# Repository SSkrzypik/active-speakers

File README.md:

The project involves active speakers inspired by the Tonsil Maestro S. The power amplifier driving the speakers consists of four TDA7294 chips. For the crossover network and sound tone adjustments, a DSP Adau1701 is used. The power supply is sourced from a toroidal transformer, and the section is enhanced with an EMI filter and a soft-start circuit. Additionally, the master speaker features an extra board that controls an OLED display and serves as a Bluetooth audio source.

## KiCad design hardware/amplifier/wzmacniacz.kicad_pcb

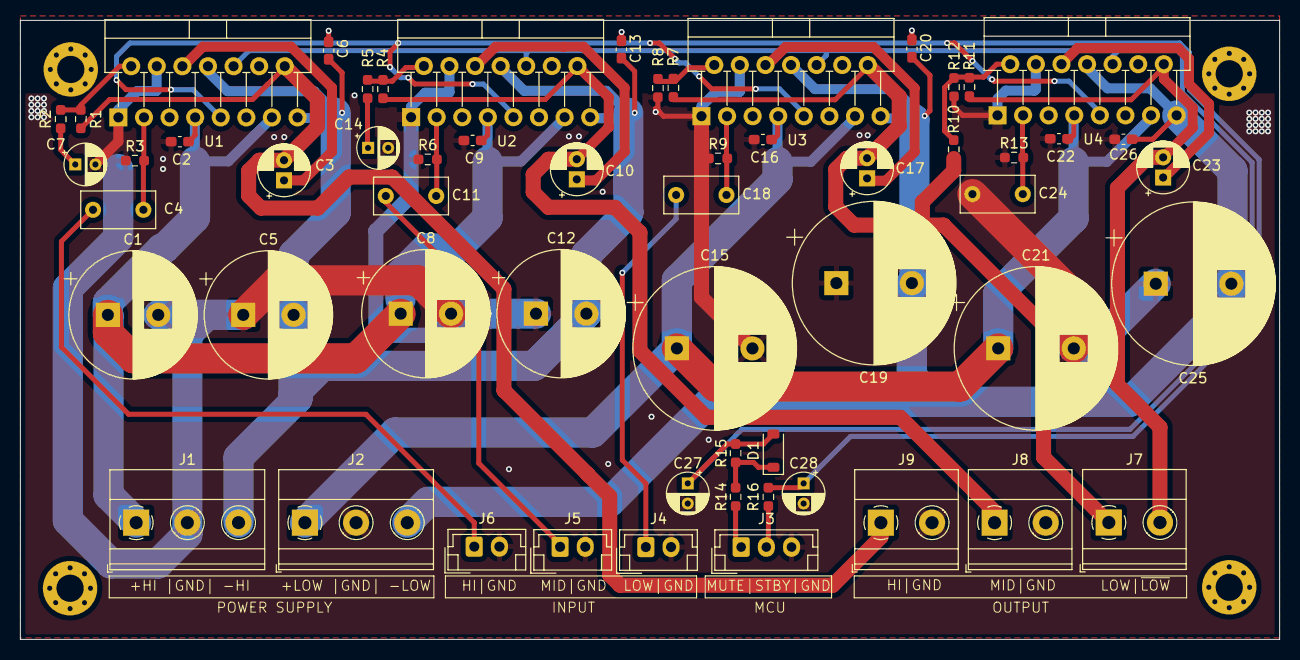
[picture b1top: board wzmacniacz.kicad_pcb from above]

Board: 2 copper layers, 125.0 x 61.4 mm, 62 parts (0 on the bottom side), 31 nets.

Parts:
C1, C5, C8, C12: 1000uF; CP_Radial_D12.5mm_P5.00mm
C2, C6, C9, C13, C16, C20, C22, C26: 100nF; C_0603_1608Metric_Pad1.08x0.95mm_HandSolder
C3, C10, C17, C23: 22uF; CP_Radial_D5.0mm_P2.00mm
C4, C11: 470nF; C_Rect_L7.2mm_W3.5mm_P5.00mm_FKS2_FKP2_MKS2_MKP2
C7, C14, C27, C28: 22uF; CP_Radial_D4.0mm_P2.00mm
C15, C19, C21, C25: 2200uF; CP_Radial_D16.0mm_P7.50mm
C18, C24: 560nF; C_Rect_L7.2mm_W3.5mm_P5.00mm_FKS2_FKP2_MKS2_MKP2
D1: 1N4148WT; D_SOD-123
H1, H2, H3, H4: MountingHole; MountingHole_2.7mm_Pad_Via
J1, J2: Conn_01x03; TerminalBlock_Phoenix_MKDS-1,5-3-5.08_1x03_P5.08mm_Horizont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
J3: Conn_01x03; JST_EH_B3B-EH-A_1x03_P2.50mm_Vertical
J4, J5, J6: Conn_01x02; JST_EH_B2B-EH-A_1x02_P2.50mm_Vertical
J7, J8, J9: Conn_01x02; TerminalBlock_Phoenix_MKDS-1,5-2-5.08_1x02_P5.08mm_Horizont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
R1, R3, R4, R6, R7, R9, R10, R11, R13, R16: 22K; R_0603_1608Metric_Pad0.98x0.95mm_HandSolder
R2, R5, R8, R12: 680; R_0603_1608Metric_Pad0.98x0.95mm_HandSolder
R14: 10K; R_0603_1608Metric_Pad0.98x0.95mm_HandSolder
R15: 30K; R_0603_1608Metric_Pad0.98x0.95mm_HandSolder
U1, U2, U3, U4: TDA7294; TO-220-15_P2.54x2.54mm_StaggerOdd_Lead4.58mm_Vertical

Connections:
+VS_HI/MID: C1.1, C2.2, C8.1, C9.2, J1.1, U1.7 (+Vs), U1.13 (+Vs), U2.7 (+Vs), U2.13 (+Vs)
+VS_LOW: C15.1, C16.2, C21.1, C22.2, J2.1, U3.7 (+Vs), U3.13 (+Vs), U4.7 (+Vs), U4.13 (+Vs)
-VS_HI/MID: C5.2, C6.2, C12.2, C13.2, J1.3, U1.8 (-Vs), U1.15 (-Vs), U2.8 (-Vs), U2.15 (-Vs)
-VS_LOW: C19.2, C20.2, C25.2, C26.2, J2.3, U3.8 (-Vs), U3.15 (-Vs), U4.8 (-Vs), U4.15 (-Vs)
/CTRL_MUTE: J3.1, R14.1
/CTRL_STBY: J3.2, R16.2
/IN_HIGH: C4.1, J6.1
/IN_LOW: C18.1, J4.1
/IN_MID: C11.1, J5.1
/MUTE: C27.1, D1.2 (A), R15.2, U1.10 (MUTE), U2.10 (MUTE), U3.10 (MUTE), U4.10 (MUTE)
/OUT_HIGH: C3.2, J9.1, R1.1, U1.14
/OUT_LOW+: C17.2, J7.1, R7.1, R10.1, U3.14
/OUT_LOW-: C23.2, J7.2, R11.1, U4.14
/OUT_MID: C10.2, J8.1, R4.1, U2.14
/STBY: C28.1, R16.1, U1.9 (STBY), U2.9 (STBY), U3.9 (STBY), U4.9 (STBY)
GND: C1.2, C2.1, C5.1, C6.1, C7.2, C8.2, C9.1, C12.1, C13.1, C14.2, C15.2, C16.1, C19.1, C20.1, C21.2, C22.1, C24.1, C25.1, C26.1, C27.2, C28.2, J1.2, J2.2, J3.3, J4.2, J5.2, J6.2, J8.2, J9.2, R3.1, R6.1, R8.1, R9.1, R12.1, R13.1, U1.1 (SGND), U1.4 (SIG_GND), U2.1 (SGND), U2.4 (SIG_GND), U3.1 (SGND), U3.4 (SIG_GND), U4.1 (SGND), U4.4 (SIG_GND)
unnamed: C7.1, R2.1
unnamed: C14.1, R5.1
unnamed: D1.1 (K), R14.2, R15.1
unnamed: C4.2, R3.2, U1.3 (+)
unnamed: R1.2, R2.2, U1.2 (-)
unnamed: C3.1, U1.6 (BOOT)
unnamed: C11.2, R6.2, U2.3 (+)
unnamed: R4.2, R5.2, U2.2 (-)
unnamed: C10.1, U2.6 (BOOT)
unnamed: C18.2, R9.2, U3.3 (+)
unnamed: R7.2, R8.2, U3.2 (-)
unnamed: C17.1, U3.6 (BOOT)
unnamed: C24.2, R13.2, U4.3 (+)
unnamed: R10.2, R11.2, R12.2, U4.2 (-)
unnamed: C23.1, U4.6 (BOOT)

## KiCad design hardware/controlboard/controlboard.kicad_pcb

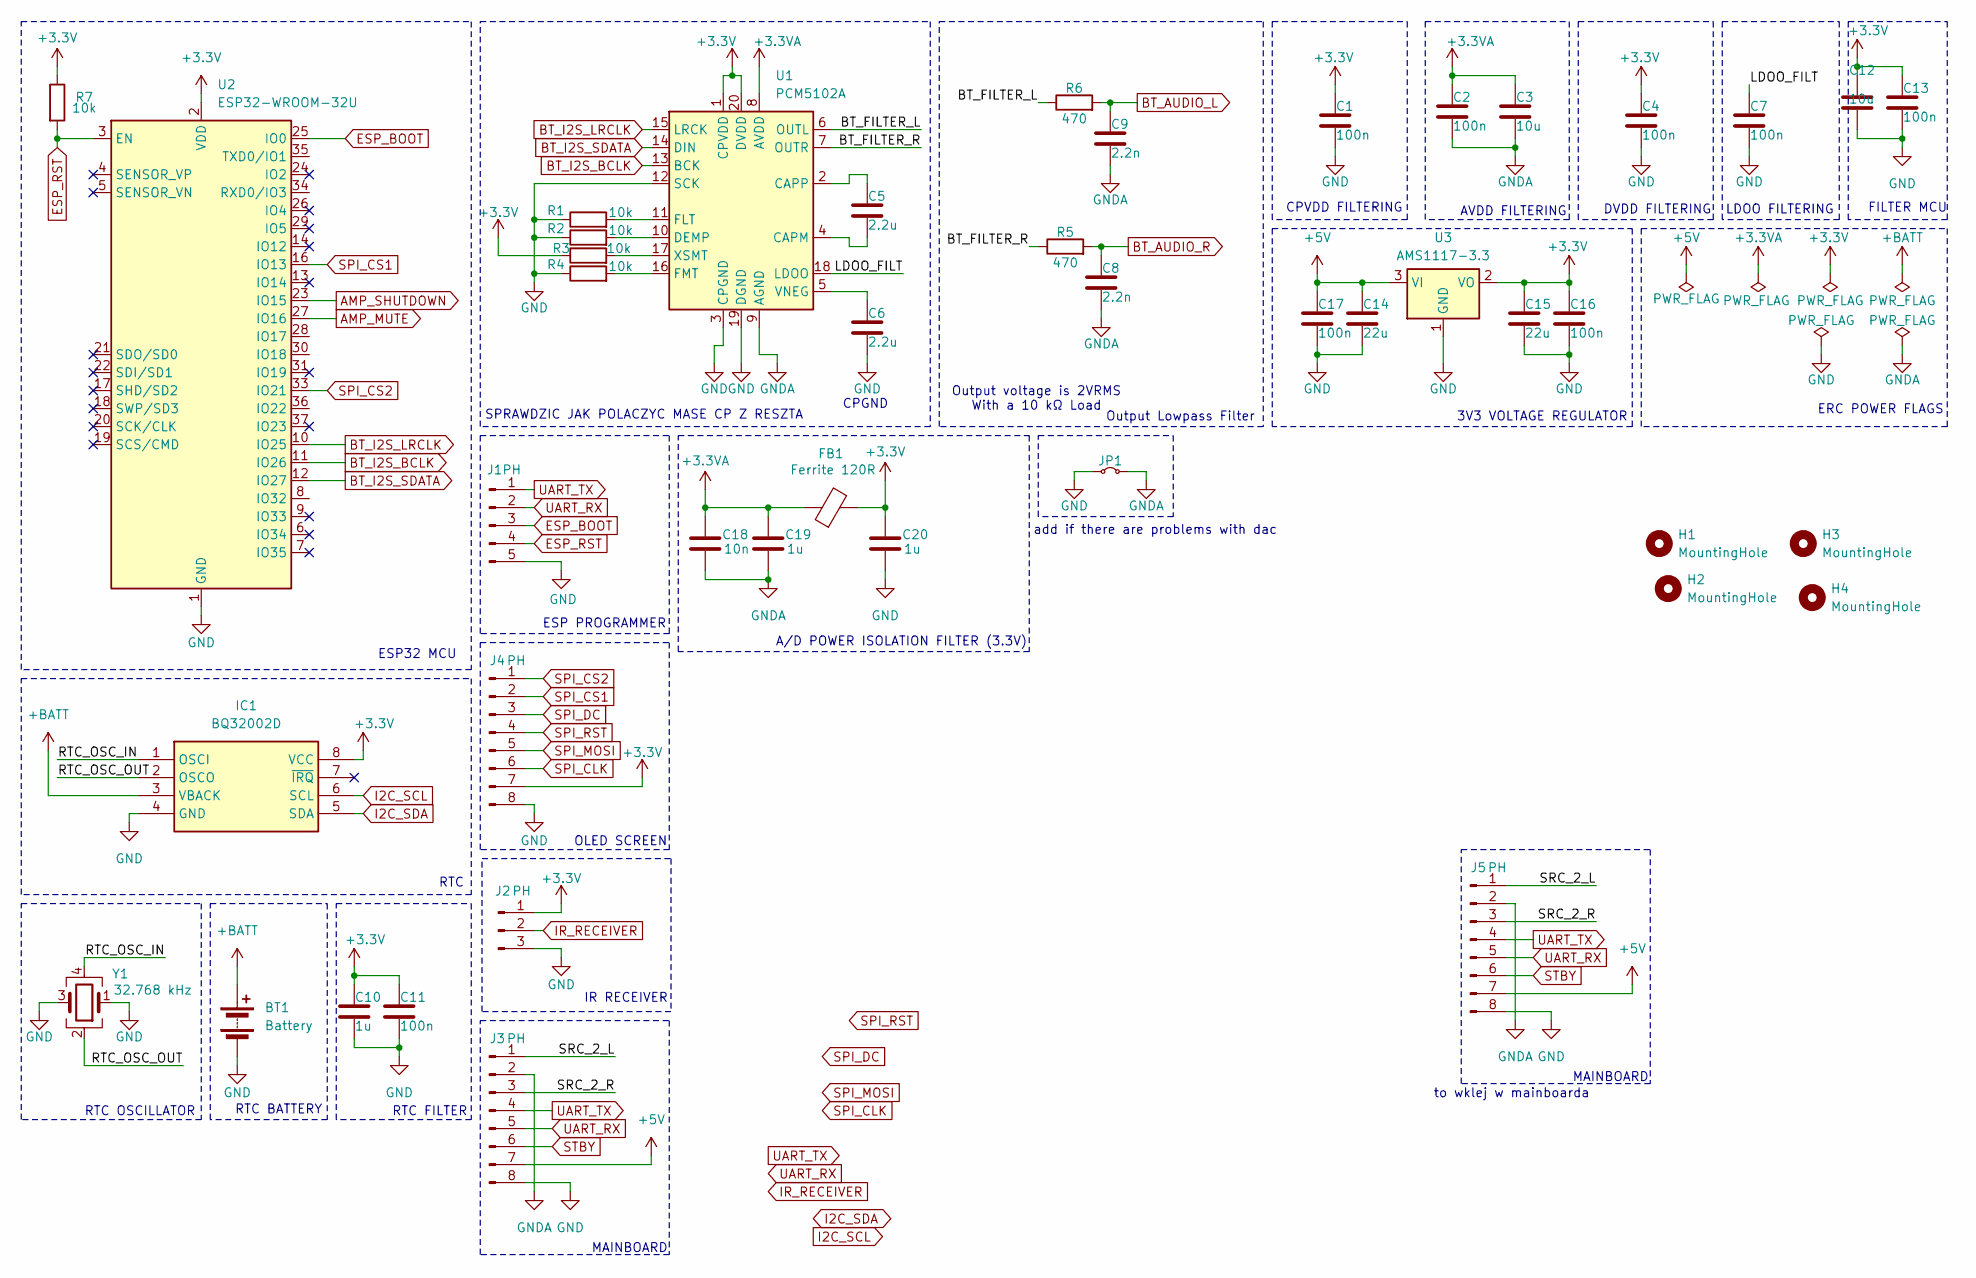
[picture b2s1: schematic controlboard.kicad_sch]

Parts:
BT1: Battery; BatteryHolder_LINX_BAT-HLD-012-SMT
C1, C2, C4, C7, C11, C13, C16, C17: 100n; C_0603_1608Metric_Pad1.08x0.95mm_HandSolder
C3, C12: 10u; C_0603_1608Metric_Pad1.08x0.95mm_HandSolder
C5, C6: 2.2u; C_0603_1608Metric_Pad1.08x0.95mm_HandSolder
C8, C9: 2.2n; C_0603_1608Metric_Pad1.08x0.95mm_HandSolder
C10, C19, C20: 1u; C_0603_1608Metric_Pad1.08x0.95mm_HandSolder
C14, C15: 22u; C_0603_1608Metric_Pad1.08x0.95mm_HandSolder
C18: 10n; C_0603_1608Metric_Pad1.08x0.95mm_HandSolder
FB1: Ferrite 120R; L_0805_2012Metric_Pad1.05x1.20mm_HandSolder
H1, H2, H3, H4: MountingHole; MountingHole_3.2mm_M3
IC1: BQ32002D; SOIC-8_3.9x4.9mm_P1.27mm; Mouser Part Number 595-BQ32002D
J1: PH; JST_PH_B5B-PH-K_1x05_P2.00mm_Vertical
J2: PH; JST_PH_B3B-PH-K_1x03_P2.00mm_Vertical
J3, J4: PH; JST_PH_B8B-PH-K_1x08_P2.00mm_Vertical
J5: PH
JP1: Jumper_2_Small_Bridged; R_1210_3225Metric_Pad1.30x2.65mm_HandSolder
R1, R2, R3, R4, R7: 10k; R_0603_1608Metric_Pad0.98x0.95mm_HandSolder
R5, R6: 470; R_0603_1608Metric_Pad0.98x0.95mm_HandSolder
U1: PCM5102A; TSSOP-20_4.4x6.5mm_P0.65mm
U2: ESP32-WROOM-32U
U3: AMS1117-3.3; SOT-223-3_TabPin2
Y1: 32.768 kHz; Crystal_SMD_7050-4Pin_7.0x5.0mm

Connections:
+3.3V: C1.1, C4.1, C10.1, C11.1, C12.1, C13.1, C15.1, C16.1, C20.1, FB1.2, IC1.8 (VCC), J2.1, J4.7, R3.1, R7.1, U1.1 (CPVDD), U1.20 (DVDD), U2.2 (VDD), U3.2 (VO)
+3.3VA: C2.1, C3.1, C18.1, C19.1, FB1.1, U1.8 (AVDD)
+5V: C14.1, C17.1, J3.7, J5.7, U3.3 (VI)
+BATT: BT1.1 (+), IC1.3 (VBACK)
/BT_FILTER_L: R6.1, U1.6 (OUTL)
/BT_FILTER_R: R5.1, U1.7 (OUTR)
/LDOO_FILT: C7.1, U1.18 (LDOO)
/RTC_OSC_IN: IC1.1 (OSCI), Y1.4
/RTC_OSC_OUT: IC1.2 (OSCO), Y1.2
/SRC_2_L: J3.1, J5.1
/SRC_2_R: J3.3, J5.3
AMP_MUTE: U2.27 (IO16)
AMP_SHUTDOWN: U2.23 (IO15)
BT_AUDIO_L: C9.1, R6.2
BT_AUDIO_R: C8.1, R5.2
BT_I2S_BCLK: U1.13 (BCK), U2.11 (IO26)
BT_I2S_LRCLK: U1.15 (LRCK), U2.10 (IO25)
BT_I2S_SDATA: U1.14 (DIN), U2.12 (IO27)
ESP_BOOT: J1.3, U2.25 (IO0)
ESP_RST: J1.4, R7.2, U2.3 (EN)
GND: BT1.2 (-), C1.2, C4.2, C6.2, C7.2, C10.2, C11.2, C12.2, C13.2, C14.2, C15.2, C16.2, C17.2, C20.2, IC1.4 (GND), J1.5, J2.3, J3.8, J4.8, J5.8, JP1.1 (A), R1.1, R2.1, R4.1, U1.3 (CPGND), U1.12 (SCK), U1.19 (DGND), U2.1 (GND), U2.15 (GND), U2.38 (GND), U2.39 (GND), U3.1 (GND), Y1.1, Y1.3
GNDA: C2.2, C3.2, C8.2, C9.2, C18.2, C19.2, J3.2, J5.2, JP1.2 (B), U1.9 (AGND)
I2C_SCL: IC1.6 (SCL)
I2C_SDA: IC1.5 (SDA)
IR_RECEIVER: J2.2
unnamed: C5.2, U1.4 (CAPM)
unnamed: C5.1, U1.2 (CAPP)
unnamed: R2.2, U1.10 (DEMP)
unnamed: R1.2, U1.11 (FLT)
unnamed: R4.2, U1.16 (FMT)
unnamed: C6.1, U1.5 (VNEG)
unnamed: R3.2, U1.17 (XSMT)
SPI_CLK: J4.6
SPI_CS1: J4.2, U2.16 (IO13)
SPI_CS2: J4.1, U2.33 (IO21)
SPI_DC: J4.3
SPI_MOSI: J4.5
SPI_RST: J4.4
STBY: J3.6, J5.6
UART_RX: J1.2, J3.5, J5.5
UART_TX: J1.1, J3.4, J5.4

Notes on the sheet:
ESP32 MCU
ERC POWER FLAGS
RTC FILTER
AVDD FILTERING
ESP PROGRAMMER
MAINBOARD
FILTER MCU
Output voltage is 2VRMS With a 10 kΩ Load
to wklej w mainboarda
RTC OSCILLATOR
3V3 VOLTAGE REGULATOR
RTC BATTERY
RTC
CPGND
add if there are problems with dac
OLED SCREEN
IR RECEIVER
Output Lowpass Filter
CPVDD FILTERING
LDOO FILTERING
SPRAWDZIC JAK POLACZYC MASE CP Z RESZTA
DVDD FILTERING
A/D POWER ISOLATION FILTER (3.3V)

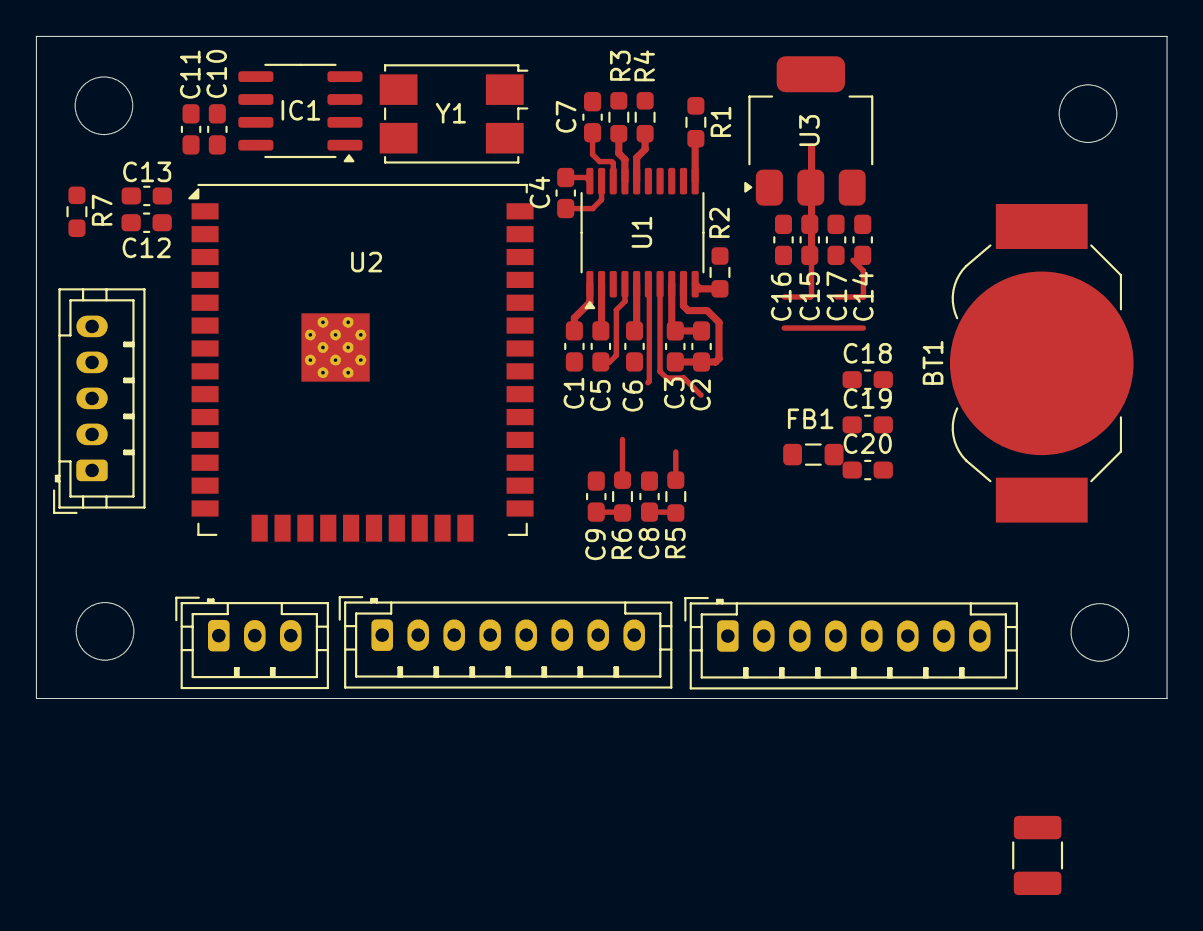
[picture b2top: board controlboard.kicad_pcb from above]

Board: 2 copper layers, 62.8 x 36.8 mm, 43 parts (0 on the bottom side), 29 nets.

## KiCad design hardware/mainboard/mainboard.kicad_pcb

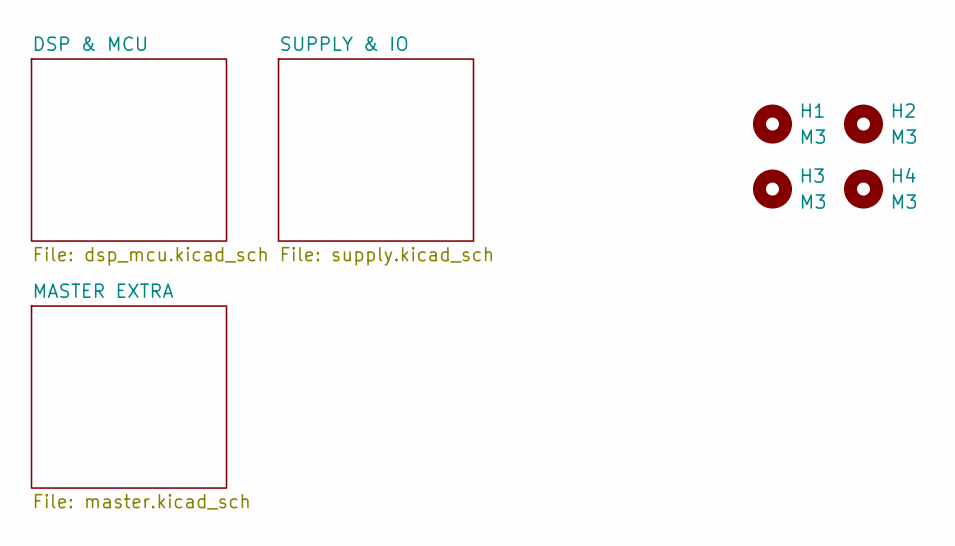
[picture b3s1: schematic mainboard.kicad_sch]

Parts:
H1, H2, H3, H4: M3; MountingHole_2.7mm_M2.5

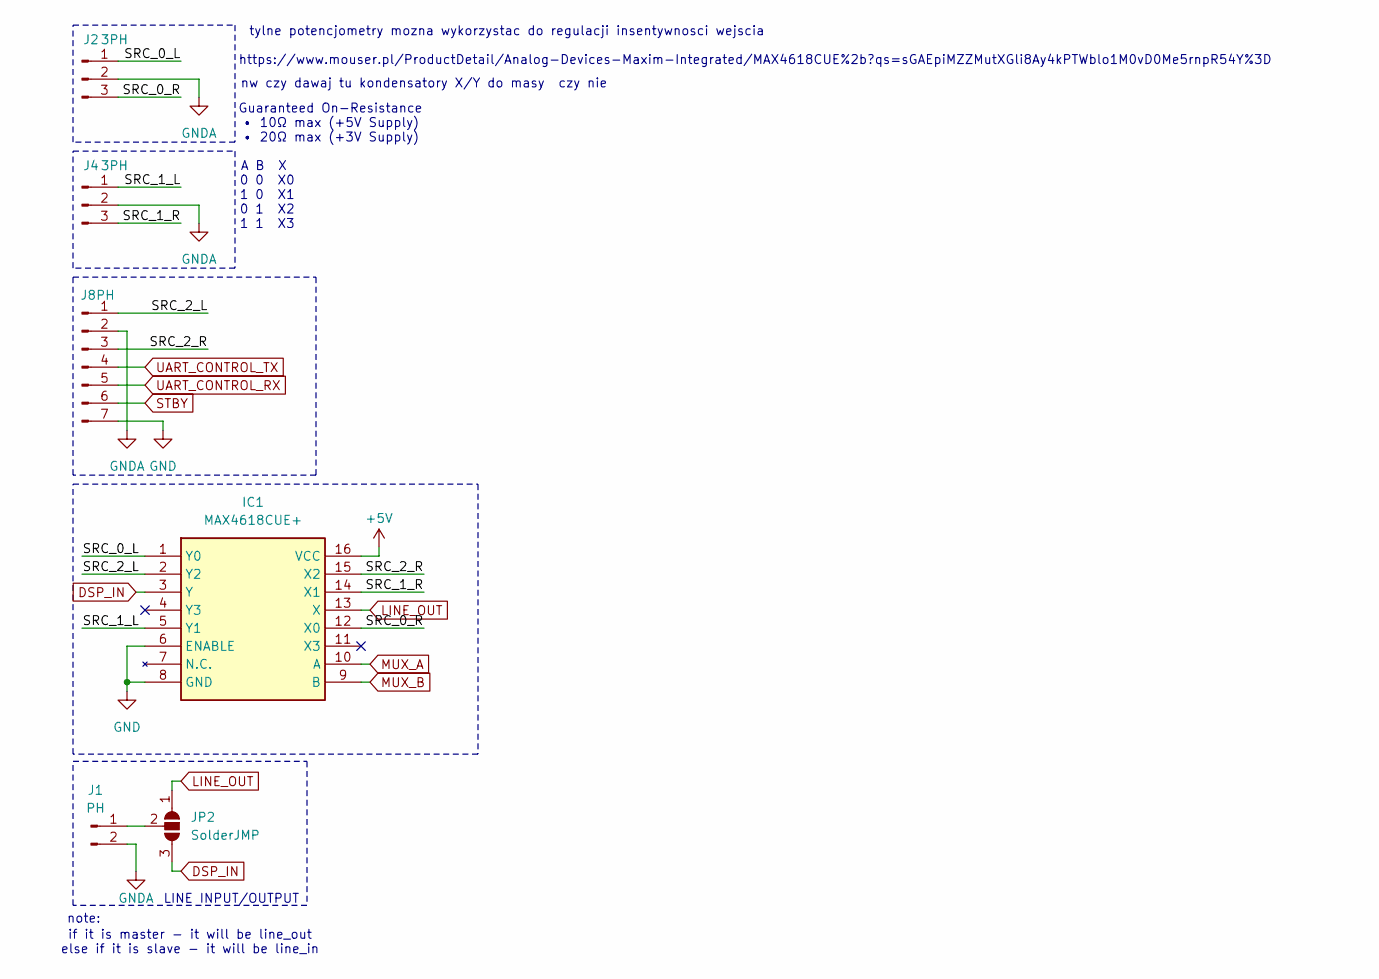
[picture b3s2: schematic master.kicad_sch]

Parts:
IC1: MAX4618CUE+; SOP65P640X110-16N; Mouser Part Number 700-MAX4618CUE
J1: PH; JST_PH_B2B-PH-K_1x02_P2.00mm_Vertical
J2, J4: 3PH; JST_PH_B3B-PH-K_1x03_P2.00mm_Vertical
J8: PH; JST_PH_B7B-PH-K_1x07_P2.00mm_Vertical
JP2: SolderJMP

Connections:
+5V: IC1.16 (VCC); also elsewhere on the board
/MASTER EXTRA/SRC_0_L: IC1.1 (Y0), J2.1
/MASTER EXTRA/SRC_0_R: IC1.12 (X0), J2.3
/MASTER EXTRA/SRC_1_L: IC1.5 (Y1), J4.1
/MASTER EXTRA/SRC_1_R: IC1.14 (X1), J4.3
/MASTER EXTRA/SRC_2_L: IC1.2 (Y2), J8.1
/MASTER EXTRA/SRC_2_R: IC1.15 (X2), J8.3
DSP_IN: IC1.3 (Y), JP2.3 (B); also elsewhere on the board
GND: IC1.6 (ENABLE), IC1.8 (GND), J8.7; also elsewhere on the board
GNDA: J1.2, J2.2, J4.2, J8.2; also elsewhere on the board
LINE_OUT: IC1.13 (X), JP2.1 (A)
MUX_A: IC1.10 (A); also elsewhere on the board
MUX_B: IC1.9 (B); also elsewhere on the board
unnamed: J1.1, JP2.2 (C)
STBY: J8.6; also elsewhere on the board
UART_CONTROL_RX: J8.5; also elsewhere on the board
UART_CONTROL_TX: J8.4; also elsewhere on the board

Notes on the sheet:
https://www.mouser.pl/ProductDetail/Analog-Devices-Maxim-Integrated/MAX4618CUE%2b?qs=sGAEpiMZZMutXGli8Ay4kPTWblo1M0vD0Me5rnpR54Y%3D
tylne potencjometry mozna wykorzystac do regulacji insentywnosci wejscia
LINE INPUT/OUTPUT
Guaranteed On-Resistance • 10Ω max (+5V Supply) • 20Ω max (+3V Supply)
A B X 0 0 X0 1 0 X1 0 1 X2 1 1 X3
note:
nw czy dawaj tu kondensatory X/Y do masy czy nie
if it is master - it will be line_out else if it is slave - it will be line_in

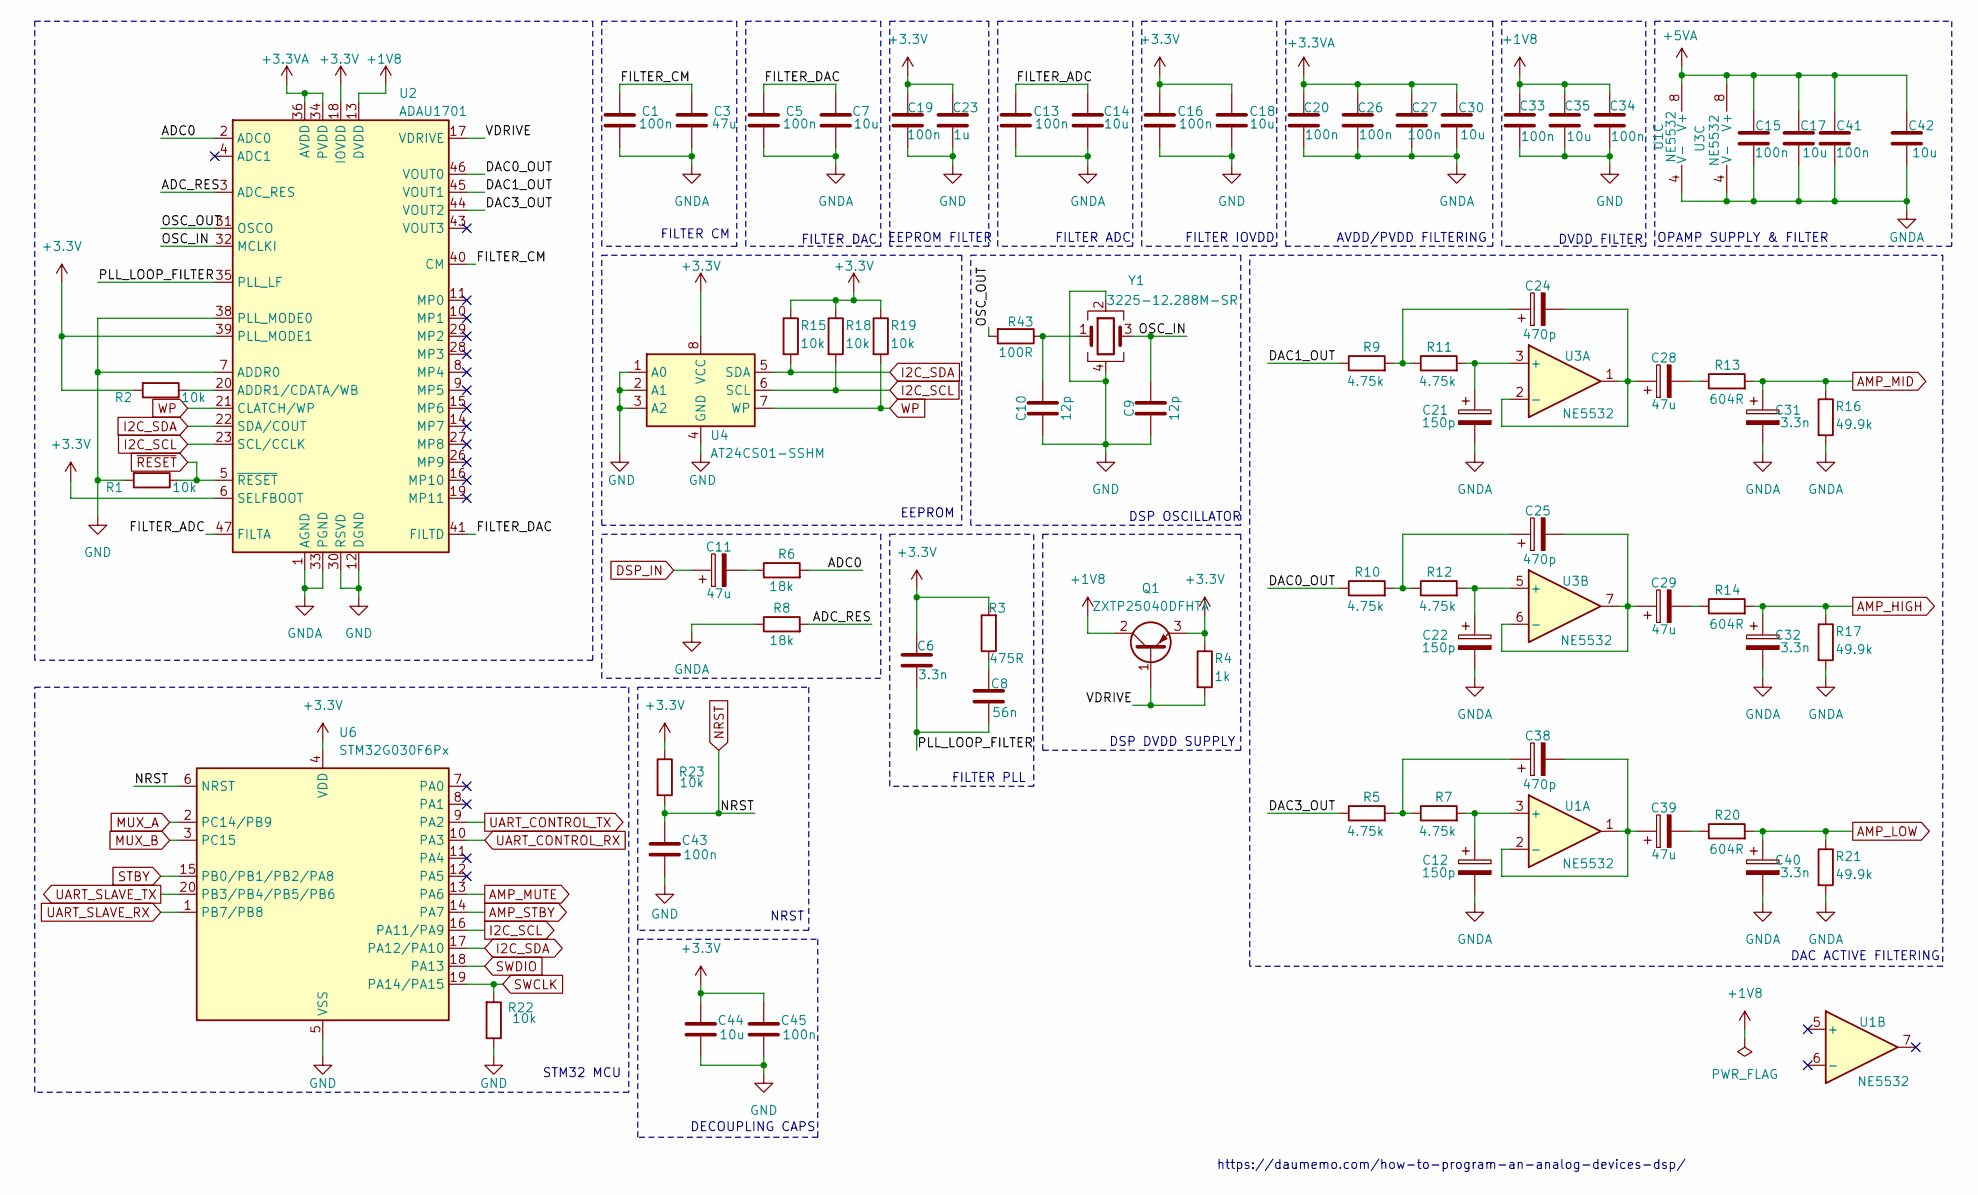
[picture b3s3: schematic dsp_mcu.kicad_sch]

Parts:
C1, C5, C13, C15, C16, C19, C20, C26, C27, C33, C34, C41, C43, C45: 100n; C_0603_1608Metric_Pad1.08x0.95mm_HandSolder
C3, C11, C28, C29, C39: 47u; C_0603_1608Metric_Pad1.08x0.95mm_HandSolder
C6, C31, C32, C40: 3.3n; C_0603_1608Metric_Pad1.08x0.95mm_HandSolder
C7, C14, C17, C18, C30, C35, C42, C44: 10u; C_0603_1608Metric_Pad1.08x0.95mm_HandSolder
C8: 56n; C_0603_1608Metric_Pad1.08x0.95mm_HandSolder
C9, C10: 12p; C_0603_1608Metric_Pad1.08x0.95mm_HandSolder
C12, C21, C22: 150p; C_0603_1608Metric_Pad1.08x0.95mm_HandSolder
C23: 1u; C_0603_1608Metric_Pad1.08x0.95mm_HandSolder
C24, C25, C38: 470p; C_0603_1608Metric_Pad1.08x0.95mm_HandSolder
Q1: ZXTP25040DFHTA; SOT-23_Handsoldering
R1, R2, R15, R18, R19, R22, R23: 10k; R_0603_1608Metric_Pad0.98x0.95mm_HandSolder
R3: 475R; R_0603_1608Metric_Pad0.98x0.95mm_HandSolder
R4: 1k; R_0603_1608Metric_Pad0.98x0.95mm_HandSolder
R5, R7, R9, R10, R11, R12: 4.75k; R_0603_1608Metric_Pad0.98x0.95mm_HandSolder
R6, R8: 18k; R_0603_1608Metric_Pad0.98x0.95mm_HandSolder
R13, R14, R20: 604R; R_0603_1608Metric_Pad0.98x0.95mm_HandSolder
R16, R17, R21: 49.9k; R_0603_1608Metric_Pad0.98x0.95mm_HandSolder
R43: 100R; R_0603_1608Metric_Pad0.98x0.95mm_HandSolder
U1, U3: NE5532; SOIC-8-1EP_3.9x4.9mm_P1.27mm_EP2.29x3mm
U2: ADAU1701; LQFP-48-1EP_7x7mm_P0.5mm_EP3.6x3.6mm_ThermalVias
U4: AT24CS01-SSHM; SOIC-8-1EP_3.9x4.9mm_P1.27mm_EP2.41x3.3mm_ThermalVias
U6: STM32G030F6Px; TSSOP-20_4.4x6.5mm_P0.65mm
Y1: 3225-12.288M-SR; Crystal_SMD_SeikoEpson_TSX3225-4Pin_3.2x2.5mm

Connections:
+1V8: C33.1, C34.1, C35.1, Q1.2 (C), U2.13 (DVDD), U2.24 (DVDD)
+3.3V: C6.2, C16.1, C18.1, C19.1, C23.1, C44.1, C45.1, Q1.3 (E), R2.2, R3.2, R4.1, R15.1, R18.1, R19.1, R23.1, U2.6 (SELFBOOT), U2.18 (IOVDD), U2.39 (PLL_MODE1), U4.8 (VCC), U6.4 (VDD); also elsewhere on the board
+3.3VA: C20.1, C26.1, C27.1, C30.1, U2.34 (PVDD), U2.36 (AVDD), U2.48 (AVDD); also elsewhere on the board
+5VA: C15.1, C17.1, C41.1, C42.1, U1.8 (V+), U3.8 (V+); also elsewhere on the board
/DSP & MCU/ADC0: R6.2, U2.2 (ADC0)
/DSP & MCU/ADC_RES: R8.2, U2.3 (ADC_RES)
/DSP & MCU/DAC0_OUT: R10.1, U2.46 (VOUT0)
/DSP & MCU/DAC1_OUT: R9.1, U2.45 (VOUT1)
/DSP & MCU/DAC3_OUT: R5.1, U2.44 (VOUT2)
/DSP & MCU/FILTER_ADC: C13.1, C14.1, U2.47 (FILTA)
/DSP & MCU/FILTER_CM: C1.1, C3.1, U2.40 (CM)
/DSP & MCU/FILTER_DAC: C5.1, C7.1, U2.41 (FILTD)
/DSP & MCU/OSC_IN: C9.2, U2.32 (MCLKI), Y1.3
/DSP & MCU/OSC_OUT: R43.2, U2.31 (OSCO)
/DSP & MCU/PLL_LOOP_FILTER: C6.1, C8.1, U2.35 (PLL_LF)
/DSP & MCU/VDRIVE: Q1.1 (B), R4.2, U2.17 (VDRIVE)
AMP_HIGH: C32.1, R14.2, R17.1; also elsewhere on the board
AMP_LOW: C40.1, R20.2, R21.1; also elsewhere on the board
AMP_MID: C31.1, R13.2, R16.1; also elsewhere on the board
AMP_MUTE: U6.13 (PA6); also elsewhere on the board
AMP_STBY: U6.14 (PA7); also elsewhere on the board
DSP_IN: C11.1; also elsewhere on the board
GND: C9.1, C10.1, C16.2, C18.2, C19.2, C23.2, C33.2, C34.2, C35.2, C43.2, C44.2, C45.2, R1.2, R22.1, U2.7 (ADDR0), U2.12 (DGND), U2.25 (DGND), U2.30 (RSVD), U2.38 (PLL_MODE0), U4.1 (A0), U4.2 (A1), U4.3 (A2), U4.4 (GND), U6.5 (VSS), Y1.2, Y1.4; also elsewhere on the board
GNDA: C1.2, C3.2, C5.2, C7.2, C12.2, C13.2, C14.2, C15.2, C17.2, C20.2, C21.2, C22.2, C26.2, C27.2, C30.2, C31.2, C32.2, C40.2, C41.2, C42.2, R8.1, R16.2, R17.2, R21.2, U1.4 (V-), U2.1 (AGND), U2.33 (PGND), U2.37 (AGND), U2.42 (AGND), U3.4 (V-); also elsewhere on the board
I2C_SCL: R18.2, U2.23 (SCL/CCLK), U4.6 (SCL), U6.16 (PA11/PA9); also elsewhere on the board
I2C_SDA: R15.2, U2.22 (SDA/COUT), U4.5 (SDA), U6.17 (PA12/PA10); also elsewhere on the board
MUX_A: U6.2 (PC14/PB9); also elsewhere on the board
MUX_B: U6.3 (PC15); also elsewhere on the board
NRST: C43.1, R23.2, U6.6 (NRST); also elsewhere on the board
unnamed: C8.2, R3.1
unnamed: C10.2, R43.1, Y1.1
unnamed: C11.2, R6.1
unnamed: C24.1, R9.2, R11.1
unnamed: C25.1, R10.2, R12.1
unnamed: C28.2, R13.1
unnamed: C29.2, R14.1
unnamed: C38.1, R5.2, R7.1
unnamed: C39.2, R20.1
unnamed: C12.1, R7.2, U1.3 (+)
unnamed: C38.2, C39.1, U1.1, U1.2 (-)
unnamed: R2.1, U2.20 (ADDR1/CDATA/WB)
unnamed: C21.1, R11.2, U3.3 (+)
unnamed: C24.2, C28.1, U3.1, U3.2 (-)
unnamed: C22.1, R12.2, U3.5 (+)
unnamed: C25.2, C29.1, U3.6 (-), U3.7
STBY: U6.15 (PB0/PB1/PB2/PA8); also elsewhere on the board
SWCLK: R22.2, U6.19 (PA14/PA15); also elsewhere on the board
SWDIO: U6.18 (PA13); also elsewhere on the board
UART_CONTROL_RX: U6.10 (PA3); also elsewhere on the board
UART_CONTROL_TX: U6.9 (PA2); also elsewhere on the board
UART_SLAVE_RX: U6.1 (PB7/PB8); also elsewhere on the board
UART_SLAVE_TX: U6.20 (PB3/PB4/PB5/PB6); also elsewhere on the board
WP: R19.2, U2.21 (CLATCH/WP), U4.7 (WP); also elsewhere on the board
~RESET: R1.1, U2.5 (~RESET); also elsewhere on the board

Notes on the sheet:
EEPROM
DAC ACTIVE FILTERING
DECOUPLING CAPS
AVDD/PVDD FILTERING
STM32 MCU
FILTER PLL
DVDD FILTER
https://daumemo.com/how-to-program-an-analog-devices-dsp/
FILTER DAC
OPAMP SUPPLY & FILTER
EEPROM FILTER
FILTER ADC
FILTER CM
DSP OSCILLATOR
FILTER IOVDD
DSP DVDD SUPPLY
NRST

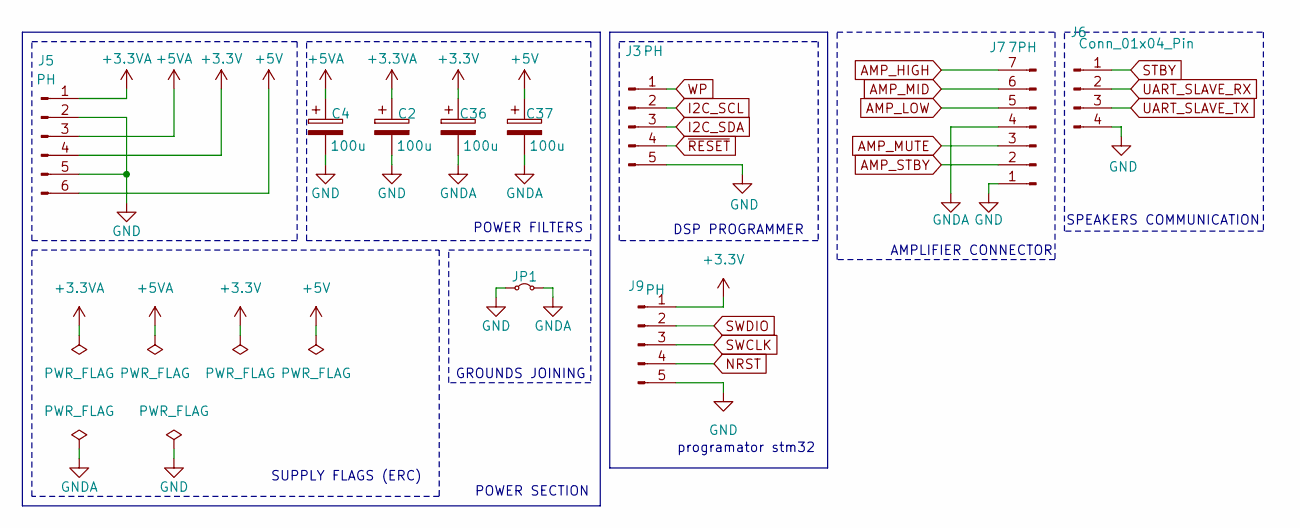
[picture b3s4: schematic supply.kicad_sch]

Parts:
C2, C4, C36, C37: 100u; CP_Elec_5x5.3
J3, J9: PH; JST_PH_B5B-PH-K_1x05_P2.00mm_Vertical
J5: PH; JST_PH_B6B-PH-K_1x06_P2.00mm_Vertical
J6: Conn_01x04_Pin; JST_PH_B4B-PH-K_1x04_P2.00mm_Vertical
J7: 7PH; JST_PH_B7B-PH-K_1x07_P2.00mm_Vertical
JP1: Jumper_2_Small_Bridged; R_1206_3216Metric_Pad1.30x1.75mm_HandSolder

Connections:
+3.3V: C36.1, J5.4, J9.1; also elsewhere on the board
+3.3VA: C2.1, J5.1; also elsewhere on the board
+5V: C37.1, J5.6; also elsewhere on the board
+5VA: C4.1, J5.3; also elsewhere on the board
AMP_HIGH: J7.7; also elsewhere on the board
AMP_LOW: J7.5; also elsewhere on the board
AMP_MID: J7.6; also elsewhere on the board
AMP_MUTE: J7.3; also elsewhere on the board
AMP_STBY: J7.2; also elsewhere on the board
GND: C2.2, C4.2, J3.5, J5.2, J5.5, J6.4, J7.1, J9.5, JP1.1 (A); also elsewhere on the board
GNDA: C36.2, C37.2, J7.4, JP1.2 (B); also elsewhere on the board
I2C_SCL: J3.2; also elsewhere on the board
I2C_SDA: J3.3; also elsewhere on the board
NRST: J9.4; also elsewhere on the board
STBY: J6.1; also elsewhere on the board
SWCLK: J9.3; also elsewhere on the board
SWDIO: J9.2; also elsewhere on the board
UART_SLAVE_RX: J6.2; also elsewhere on the board
UART_SLAVE_TX: J6.3; also elsewhere on the board
WP: J3.1; also elsewhere on the board
~RESET: J3.4; also elsewhere on the board

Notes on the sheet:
SUPPLY FLAGS (ERC)
programator stm32
GROUNDS JOINING
POWER SECTION
DSP PROGRAMMER
SPEAKERS COMMUNICATION
POWER FILTERS
AMPLIFIER CONNECTOR

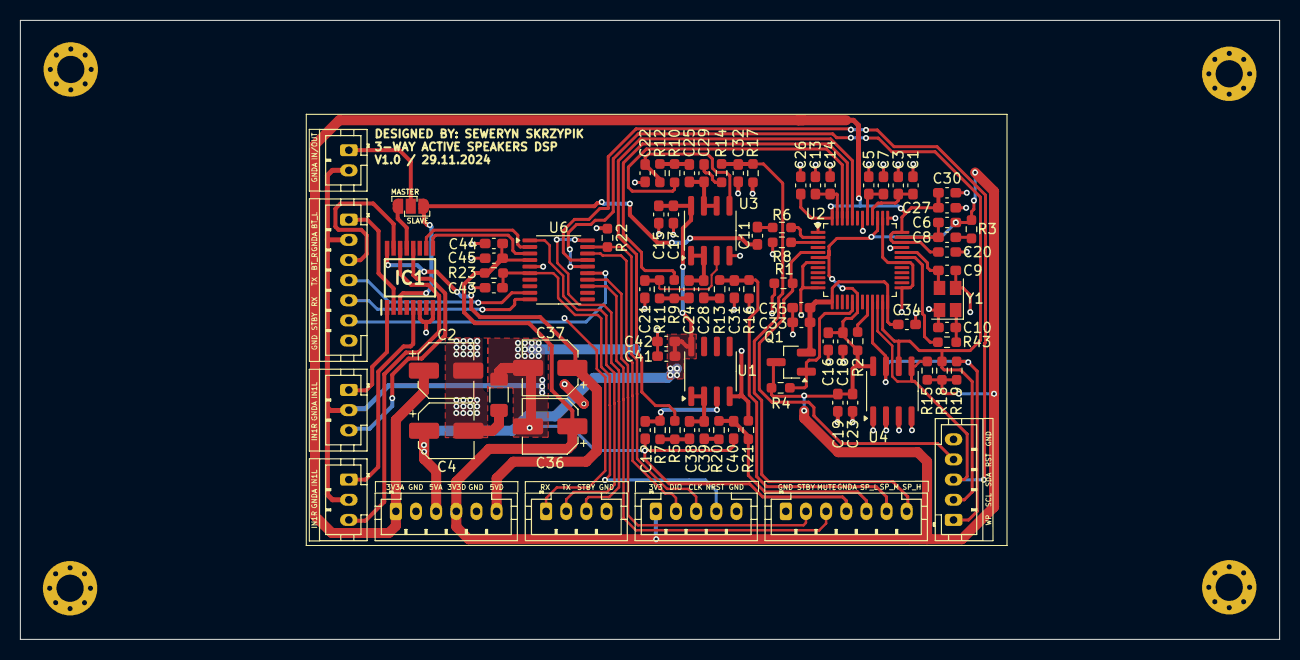
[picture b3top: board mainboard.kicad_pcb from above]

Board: 2 copper layers, 125.0 x 61.4 mm, 92 parts (0 on the bottom side), 63 nets.
